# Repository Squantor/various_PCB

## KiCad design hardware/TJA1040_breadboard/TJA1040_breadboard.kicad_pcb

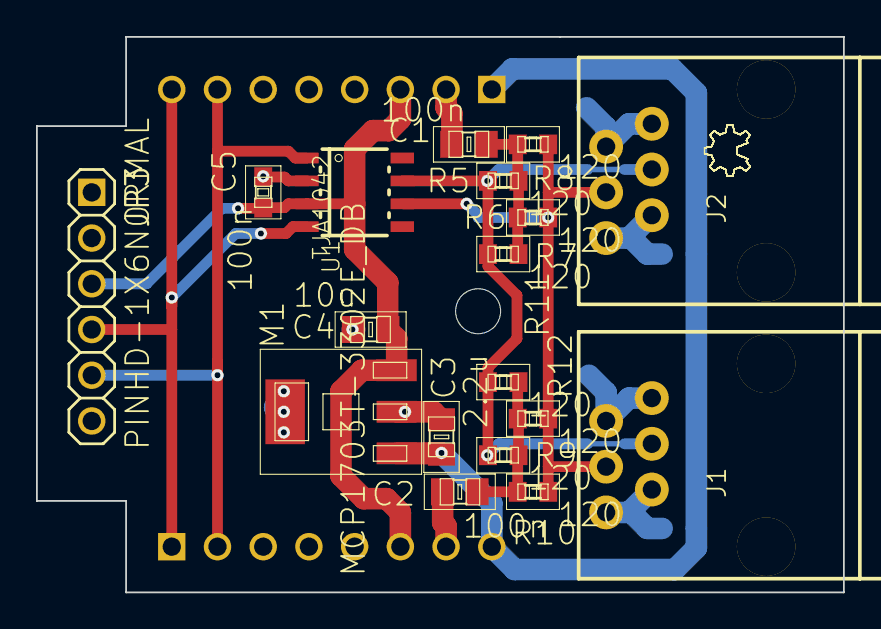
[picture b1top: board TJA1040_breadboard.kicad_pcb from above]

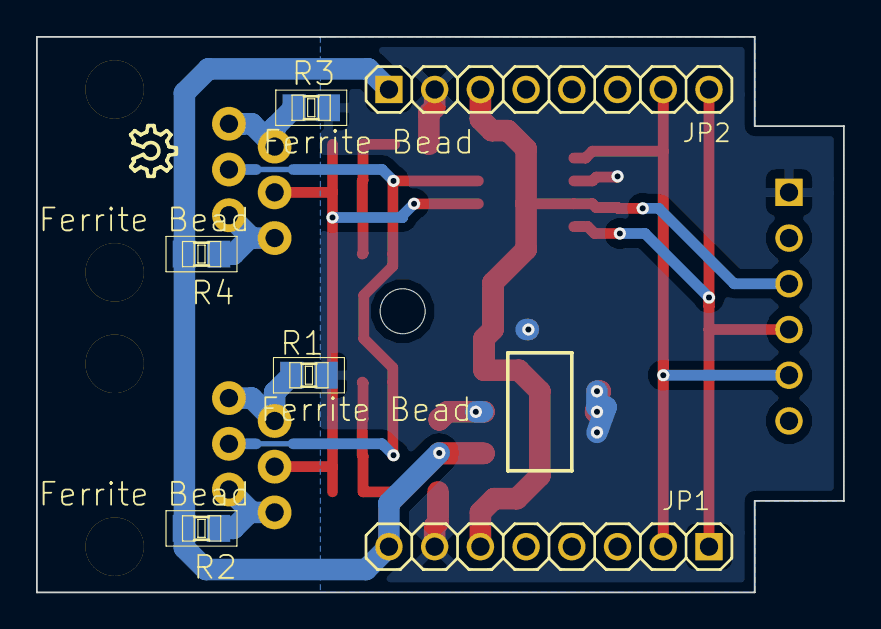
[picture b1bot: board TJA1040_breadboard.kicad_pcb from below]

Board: 2 copper layers, 44.8 x 30.9 mm, 25 parts (5 on the bottom side), 13 nets.

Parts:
C1, C2: 100n; SquantorRCL-C0805
C3: 2.2u; SquantorRCL-C0805
C4: 10u; SquantorRCL-C0805
C5: 100n; SquantorRCL-C0603
J1, J2: SquantBus_RJ11; SquantBus-RJ11
JP1, JP2: PINHD-1X8TH_NORMAL; SquantorConnectors-1X08
JP3: PINHD-1X6NORMAL; SquantorConnectors-1X06
LOGO1: OSHW_LOGO_8MILX0100-NT; ohw-logo-OSHW_8X100_NOTEXT
M1: MCP1703T-3302E_DB; SquantorMicrochip-SOT223
R1, R2, R3, R4: Ferrite Bead; SquantorRCL-R0805
R5, R6, R7, R8, R9, R10, R11, R12: 120; SquantorRCL-R0603
U1: TJA1042; SOT96-1

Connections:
+5V: C4.1, C5.2, JP1.6, JP2.3, JP3.3, M1.3, U1.3
+BATT: C3.1, JP1.8, JP2.1, M1.1, R2.2, R4.2
CAN_H: J1.4, J2.4, R5.1, R7.1, R9.1, R11.1, U1.7
CAN_L: J1.3, J2.3, R6.2, R8.2, R10.2, R12.2, U1.6
CAN_RX: JP1.1, JP2.8, JP3.4, U1.4
CAN_TX: JP1.2, JP2.7, JP3.5, U1.1
GND: C1.2, C2.1, C3.2, C4.2, C5.1, JP1.7, JP2.2, JP3.1, M1.2, M1.4, R1.2, R3.2, U1.2
unnamed: C1.1, R5.2, R6.1, R7.2, R8.1
unnamed: C2.2, R9.2, R10.1, R11.2, R12.1
unnamed: J1.1, J1.2, R2.1
unnamed: J1.5, J1.6, R1.1
unnamed: J2.1, J2.2, R4.1
unnamed: J2.5, J2.6, R3.1

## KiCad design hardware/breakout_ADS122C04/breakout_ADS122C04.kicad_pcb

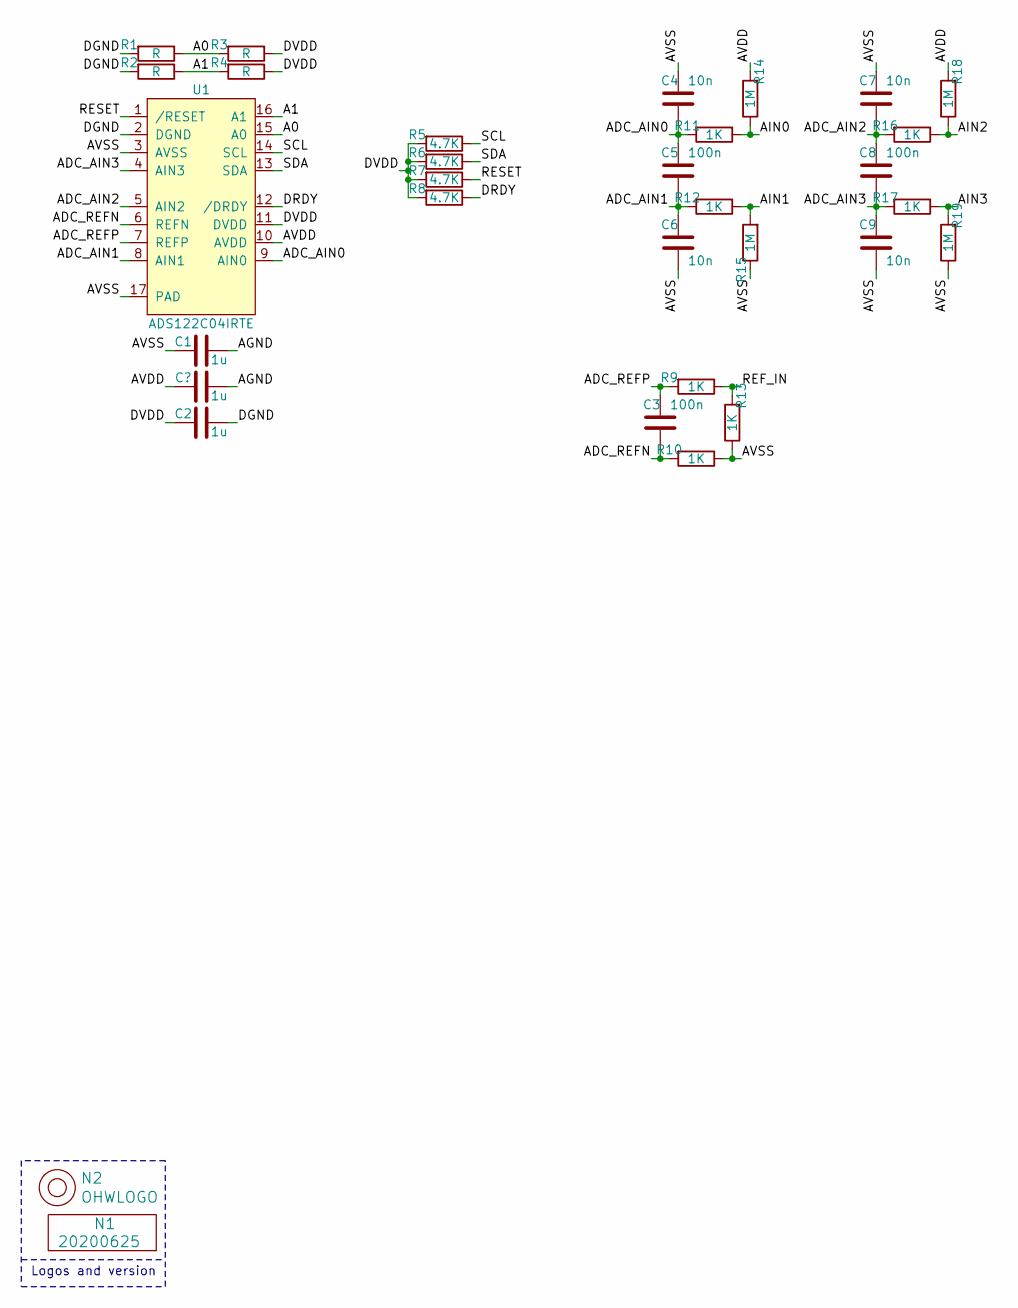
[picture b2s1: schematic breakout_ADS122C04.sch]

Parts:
C1, C2: 1u; C_0402
C3, C5, C8: 100n; C_0402
C4, C6, C7, C9: 10n; C_0402
N1: 20200625; Label_Generic
N2: OHWLOGO; OSHW-Symbol_6.7x6mm_SilkScreen
R1, R2, R3, R4: R; R_0402_hand
R5, R6, R7, R8: 4.7K; R_0402_hand
R9, R10, R11, R12, R13, R16, R17: 1K; R_0402_hand
R14, R15, R18, R19: 1M; R_0402_hand
U1: ADS122C04IRTE; QFN-16-1EP_3x3mm_P0.5mm_EP1.45x1.45mm

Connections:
/A0: R1.1, R3.2, U1.15 (A0)
/A1: R2.1, R4.2, U1.16 (A1)
/ADC_AIN0: C4.2, C5.1, R11.2, U1.9 (AIN0)
/ADC_AIN1: C5.2, C6.1, R12.2, U1.8 (AIN1)
/ADC_AIN2: C7.2, C8.1, R16.2, U1.5 (AIN2)
/ADC_AIN3: C8.2, C9.1, R17.2, U1.4 (AIN3)
/ADC_REFN: C3.2, R10.2, U1.6 (REFN)
/ADC_REFP: C3.1, R9.2, U1.7 (REFP)
/AGND: C1.1; also elsewhere on the board
/AIN0: R11.1, R14.1
/AIN1: R12.1, R15.2
/AIN2: R16.1, R18.1
/AIN3: R17.1, R19.2
/AVDD: R14.2, R18.2, U1.10 (AVDD); also elsewhere on the board
/AVSS: C1.2, C4.1, C6.2, C7.1, C9.2, R10.1, R13.1, R15.1, R19.1, U1.3 (AVSS), U1.17 (PAD)
/DGND: C2.1, R1.2, R2.2, U1.2 (DGND)
/DRDY: R8.1, U1.12 (/DRDY)
/DVDD: C2.2, R3.1, R4.1, R5.2, R6.2, R7.2, R8.2, U1.11 (DVDD)
/REF_IN: R9.1, R13.2
/RESET: R7.1, U1.1 (/RESET)
/SCL: R5.1, U1.14 (SCL)
/SDA: R6.1, U1.13 (SDA)

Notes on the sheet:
Logos and version

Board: 2 copper layers, 32 parts (0 on the bottom side), 22 nets, no tracks yet.

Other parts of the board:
C10: 1u; C_0402

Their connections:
/AGND: C10.1; also elsewhere on the board
/AVDD: C10.2; also elsewhere on the board

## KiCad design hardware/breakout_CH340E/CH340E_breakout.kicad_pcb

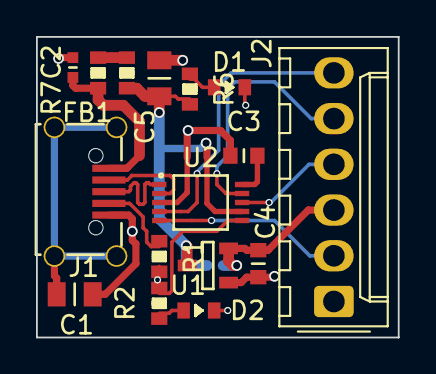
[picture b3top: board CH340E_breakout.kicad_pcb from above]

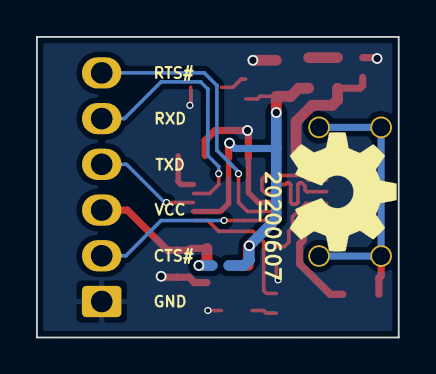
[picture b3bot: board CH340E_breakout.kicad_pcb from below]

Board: 2 copper layers, 20.1 x 16.7 mm, 18 parts (2 on the bottom side), 16 nets.

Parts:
C1: 100n; C_0805
C2: 100n; C_0402
C3, C4: 1u; C_0603
C5: 10u; C_0805
D1: GRN; D_0603_hand
D2: RED; D_0603_hand
FB1: 600; R_0603_hand
J1: USB-ID; USB-muB-SMD_TH
J2: FTDI_PINS_1X06_input; Molex_KK-254_AE-6410-06A_1x06_P2.54mm_Vertical_FTDI_UART
N1: OHWLOGO; OSHW-Symbol_6.7x6mm_SilkScreen
N2: 20200607; Label_Generic
R1: 0; R_0603_hand
R2, R6: 1K; R_0603_hand
R7: Fuse; R_0603_hand
U1: MCP1702-CB; SOT23-3-Microchip-TT
U2: CH340E; MSOP-10

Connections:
/ACT: R2.2, U2.6
/CTSI: J2.2, U2.5
/RTSO: J2.6, U2.4
/RXI: J2.5, U2.9
/TXO: J2.4, U2.8
/USB_DM: J1.2, U2.2
/USB_DP: J1.3, U2.1
/V3: C3.2, C4.1, U1.2, U2.7, U2.10
/VBUS: C2.1, J1.1, R7.2
/VDD: C5.1, FB1.1, J2.3, R6.2, U1.3
/VSS: C1.2, C2.2, C3.1, C4.2, C5.2, D1.1, D2.1, J1.5, J2.1, R1.2, U1.1, U2.3
unnamed: C1.1, J1.S
unnamed: D1.2, R6.1
unnamed: D2.2, R2.1
unnamed: FB1.2, R7.1
unnamed: J1.4, R1.1

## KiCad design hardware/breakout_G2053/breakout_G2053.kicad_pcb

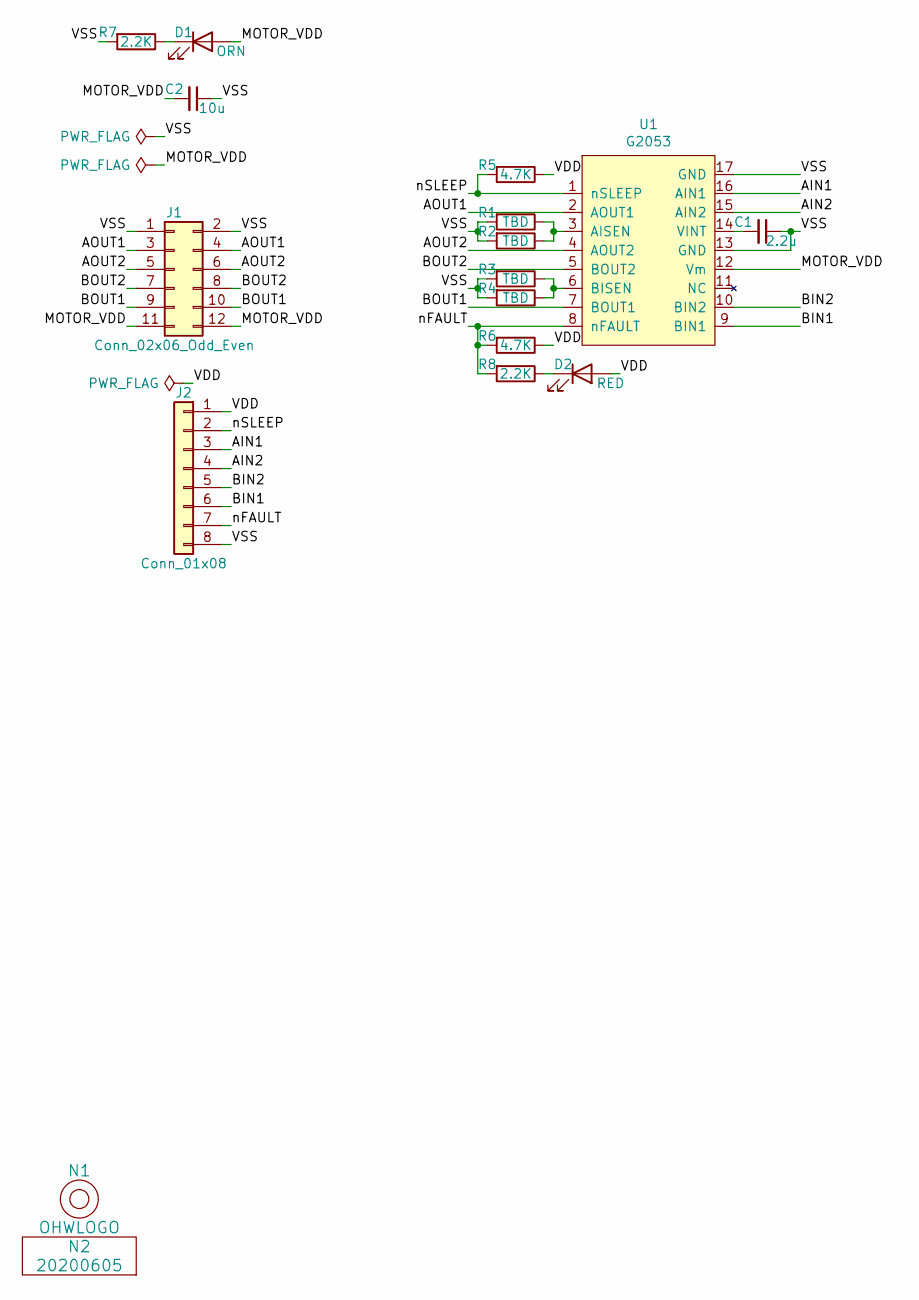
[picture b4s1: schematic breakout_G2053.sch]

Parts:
C1: 2.2u; C_0805
C2: 10u; C_0805
D1: ORN; LED_0603_hand
D2: RED; LED_0603_hand
J1: Conn_02x06_Odd_Even; PinHeader_2x06_P2.54mm_Vertical
J2: Conn_01x08; PinHeader_1x08_P2.54mm_Vertical
N1: OHWLOGO; OSHW-Symbol_6.7x6mm_SilkScreen
N2: 20200605; Label_Generic
R1, R2, R3, R4: TBD; R_1206
R5, R6: 4.7K; R_0603_hand
R7, R8: 2.2K; R_0603_hand
U1: G2053; TSSOP-16_EP

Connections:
/AIN1: J2.3, U1.16 (AIN1)
/AIN2: J2.4, U1.15 (AIN2)
/AOUT1: J1.3, J1.4, U1.2 (AOUT1)
/AOUT2: J1.5, J1.6, U1.4 (AOUT2)
/BIN1: J2.6, U1.9 (BIN1)
/BIN2: J2.5, U1.10 (BIN2)
/BOUT1: J1.9, J1.10, U1.7 (BOUT1)
/BOUT2: J1.7, J1.8, U1.5 (BOUT2)
/MOTOR_VDD: C2.2, D1.2 (A), J1.11, J1.12, U1.12 (Vm)
/VDD: D2.2 (A), J2.1, R5.1, R6.1
/VSS: C1.1, C2.1, J1.1, J1.2, J2.8, R1.2, R2.2, R3.2, R4.2, R7.2, U1.13 (GND), U1.17 (GND)
/nFAULT: J2.7, R6.2, R8.2, U1.8 (nFAULT)
/nSLEEP: J2.2, R5.2, U1.1 (nSLEEP)
unnamed: C1.2, U1.14 (VINT)
unnamed: D1.1 (K), R7.1
unnamed: D2.1 (K), R8.1
unnamed: R1.1, R2.1, U1.3 (AISEN)
unnamed: R3.1, R4.1, U1.6 (BISEN)

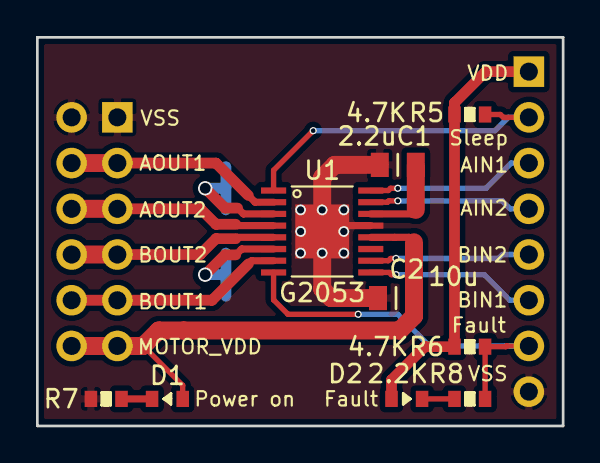
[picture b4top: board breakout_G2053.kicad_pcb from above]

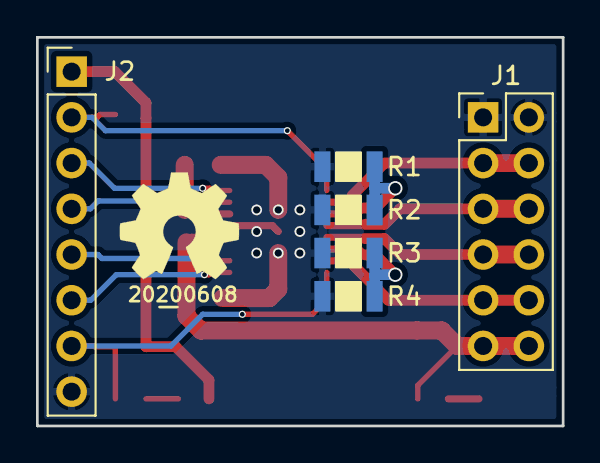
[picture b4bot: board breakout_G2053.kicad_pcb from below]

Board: 2 copper layers, 29.2 x 21.6 mm, 17 parts (8 on the bottom side), 18 nets.

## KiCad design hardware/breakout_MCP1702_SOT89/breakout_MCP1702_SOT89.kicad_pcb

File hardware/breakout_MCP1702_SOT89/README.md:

# MCP1702 SOT89 breakout board
Very simple PDIP adapter for the MCP1702 LDO
## TODO's
Still some things need to be done:
* Produce at [OSHPARK](https://oshpark.com/) (In progress)
* Assemble (TODO)
* Test & characterise (TODO)
* update Readme.md with pictures and BOM (TODO)
## BOM
## Pictures

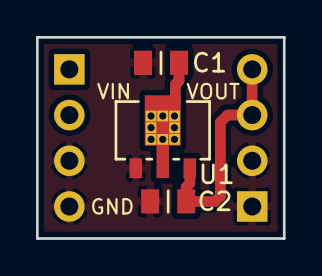
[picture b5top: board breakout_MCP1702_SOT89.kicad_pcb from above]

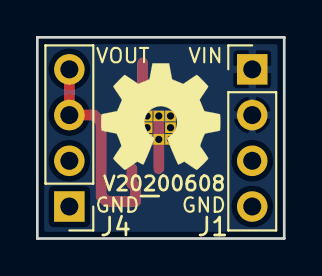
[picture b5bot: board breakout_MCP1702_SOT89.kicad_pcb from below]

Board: 2 copper layers, 13.7 x 11.2 mm, 7 parts (4 on the bottom side), 3 nets.

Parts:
C1, C2: 1u; C_0805
J1, J4: Conn_01x04; PinHeader_1x04_P2.54mm_Vertical
N1: OHWLOGO; OSHW-Symbol_6.7x6mm_SilkScreen
N2: V20200608; Label_Generic
U1: MCP1702-MB; SOT89-NXP-Viatab

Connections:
/VIN: C1.1, J1.1, J1.2, U1.2
/VOUT: C2.1, J4.3, J4.4, U1.3
/VSS: C1.2, C2.2, J1.3, J1.4, J4.1, J4.2, U1.1

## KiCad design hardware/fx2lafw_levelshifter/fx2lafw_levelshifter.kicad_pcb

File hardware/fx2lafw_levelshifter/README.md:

# FX2 Logicanalyzer level shifter
Level shifter for the cheap FX2 based logic analyzers. Connects to the input port of the LA and requires a 5V supply from the analyzer.
## TODO's
Still some things need to be done:
* schematic entry (TODO)
* PCB layout (TODO)
* Review with one night in between (TODO)
* Produce at [OSHPARK](https://oshpark.com/) (TODO)
* Assemble (TODO)
* Test & characterise (TODO)
* update Readme.md with pictures and BOM (TODO)
## BOM
* [74LVC8T45](https://assets.nexperia.com/documents/data-sheet/74LVC_LVCH8T245.pdf) octal dual supply bidirectional levelshifter

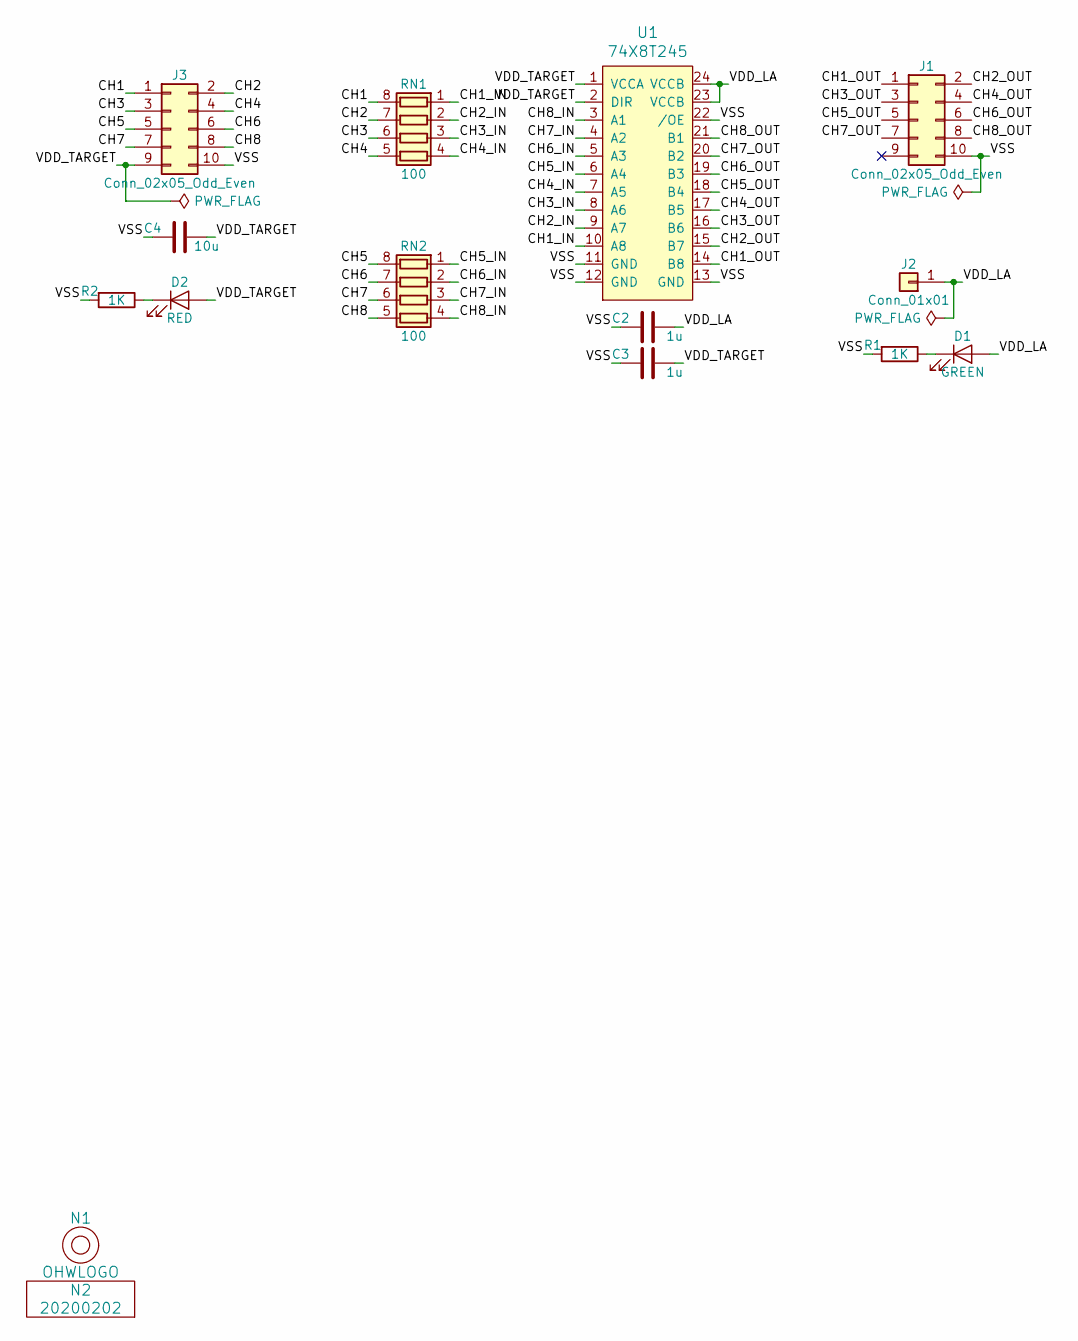
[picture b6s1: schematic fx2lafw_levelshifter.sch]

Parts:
C2, C3: 1u; C_0402
C4: 10u; C_0603
D1: GREEN; LED_0603_hand
D2: RED; LED_0603_hand
J1: Conn_02x05_Odd_Even; Header-Fem-0254-2X05-SMD-Edge
J2: Conn_01x01; Header-0254-1X01-H010
J3: Conn_02x05_Odd_Even; Header-Male-0254-2X05-SMD-Edge
N1: OHWLOGO; OSHW-Symbol_6.7x6mm_SilkScreen
N2: 20200202; Label_Generic
R1, R2: 1K; R_0402_hand
RN1, RN2: 100; R_Array_Convex_4x0402
U1: 74X8T245; SOT355-1-NXP

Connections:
/CH1: J3.1, RN1.8 (R1.2)
/CH1_IN: RN1.1 (R1.1), U1.10 (A8)
/CH1_OUT: J1.1, U1.14 (B8)
/CH2: J3.2, RN1.7 (R2.2)
/CH2_IN: RN1.2 (R2.1), U1.9 (A7)
/CH2_OUT: J1.2, U1.15 (B7)
/CH3: J3.3, RN1.6 (R3.2)
/CH3_IN: RN1.3 (R3.1), U1.8 (A6)
/CH3_OUT: J1.3, U1.16 (B6)
/CH4: J3.4, RN1.5 (R4.2)
/CH4_IN: RN1.4 (R4.1), U1.7 (A5)
/CH4_OUT: J1.4, U1.17 (B5)
/CH5: J3.5, RN2.8 (R1.2)
/CH5_IN: RN2.1 (R1.1), U1.6 (A4)
/CH5_OUT: J1.5, U1.18 (B4)
/CH6: J3.6, RN2.7 (R2.2)
/CH6_IN: RN2.2 (R2.1), U1.5 (A3)
/CH6_OUT: J1.6, U1.19 (B3)
/CH7: J3.7, RN2.6 (R3.2)
/CH7_IN: RN2.3 (R3.1), U1.4 (A2)
/CH7_OUT: J1.7, U1.20 (B2)
/CH8: J3.8, RN2.5 (R4.2)
/CH8_IN: RN2.4 (R4.1), U1.3 (A1)
/CH8_OUT: J1.8, U1.21 (B1)
/VDD_LA: C2.1, D1.2 (A), J2.1, U1.23 (VCCB), U1.24 (VCCB)
/VDD_TARGET: C3.1, C4.1, D2.2 (A), J3.9, U1.1 (VCCA), U1.2 (DIR)
/VSS: C2.2, C3.2, C4.2, J1.10, J3.10, R1.2, R2.2, U1.11 (GND), U1.12 (GND), U1.13 (GND), U1.22 (/OE)
unnamed: D1.1 (K), R1.1
unnamed: D2.1 (K), R2.1

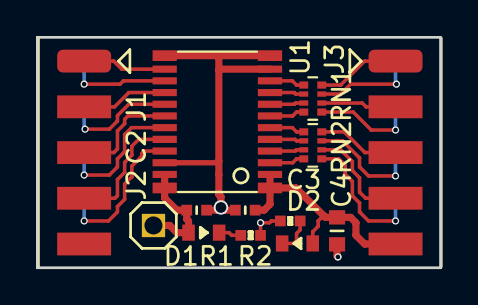
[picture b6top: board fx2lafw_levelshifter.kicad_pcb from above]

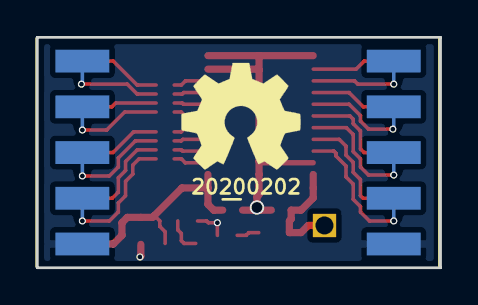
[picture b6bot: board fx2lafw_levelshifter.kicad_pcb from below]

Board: 2 copper layers, 22.4 x 12.8 mm, 15 parts (3 on the bottom side), 29 nets.

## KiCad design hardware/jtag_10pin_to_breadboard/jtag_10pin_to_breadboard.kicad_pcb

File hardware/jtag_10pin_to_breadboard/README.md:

# 10 Pin JTAG to breadboard connection
This converts the 10 pin JTAG connection that are often used on ARM development board to something a you can stick on a breadboard. Why? Well Some programmers can be put into service as a SPI device, coupled with the nice levelshifting you can do some useful things with it then.
## TODO's
Still some things need to be done:
* schematic entry (TODO)
* PCB layout (TODO)
* Review with one night in between (TODO)
* Produce at [OSHPARK](https://oshpark.com/) (TODO)
* Assemble (TODO)
* Test & characterise (TODO)
* update Readme.md with pictures and BOM (TODO)
## BOM
## Pictures

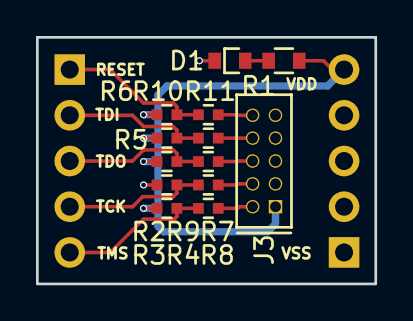
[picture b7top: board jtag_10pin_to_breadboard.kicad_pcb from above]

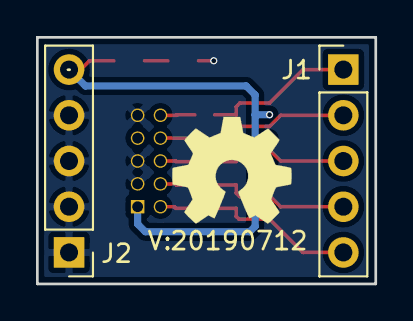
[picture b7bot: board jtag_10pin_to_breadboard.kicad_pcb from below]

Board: 2 copper layers, 18.8 x 13.7 mm, 17 parts (4 on the bottom side), 13 nets.

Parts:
D1: RED; D_0603_hand
J1, J2: Conn_01x05; PinHeader_1x05_P2.54mm_Vertical
J3: JTAG_2X05; Header-0127-2X05-H006
N1: OHWLOGO; OSHW-Symbol_6.7x6mm_SilkScreen
N2: 20190712; Label_version
R1: 4.7K; R_0603_hand
R2, R5: 100K; R_0402_hand
R3, R4, R6: 100k; R_0402_hand
R7, R8, R9, R10, R11: 100; R_0402_hand

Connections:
/RESET: J1.1, R6.2, R11.2
/TCK: J1.4, R3.2, R8.2
/TDI: J1.2, R5.2, R10.2
/TDO: J1.3, R4.2, R9.2
/TMS: J1.5, R2.2, R7.2
/VDD: J2.5, J3.1, R1.2, R2.1, R4.1, R5.1, R6.1
/VSS: D1.1, J2.1, J2.2, J2.3, J2.4, J3.3, J3.5, J3.9, R3.1
unnamed: D1.2, R1.1
unnamed: J3.2, R7.1
unnamed: J3.4, R8.1
unnamed: J3.6, R9.1
unnamed: J3.8, R10.1
unnamed: J3.10, R11.1
